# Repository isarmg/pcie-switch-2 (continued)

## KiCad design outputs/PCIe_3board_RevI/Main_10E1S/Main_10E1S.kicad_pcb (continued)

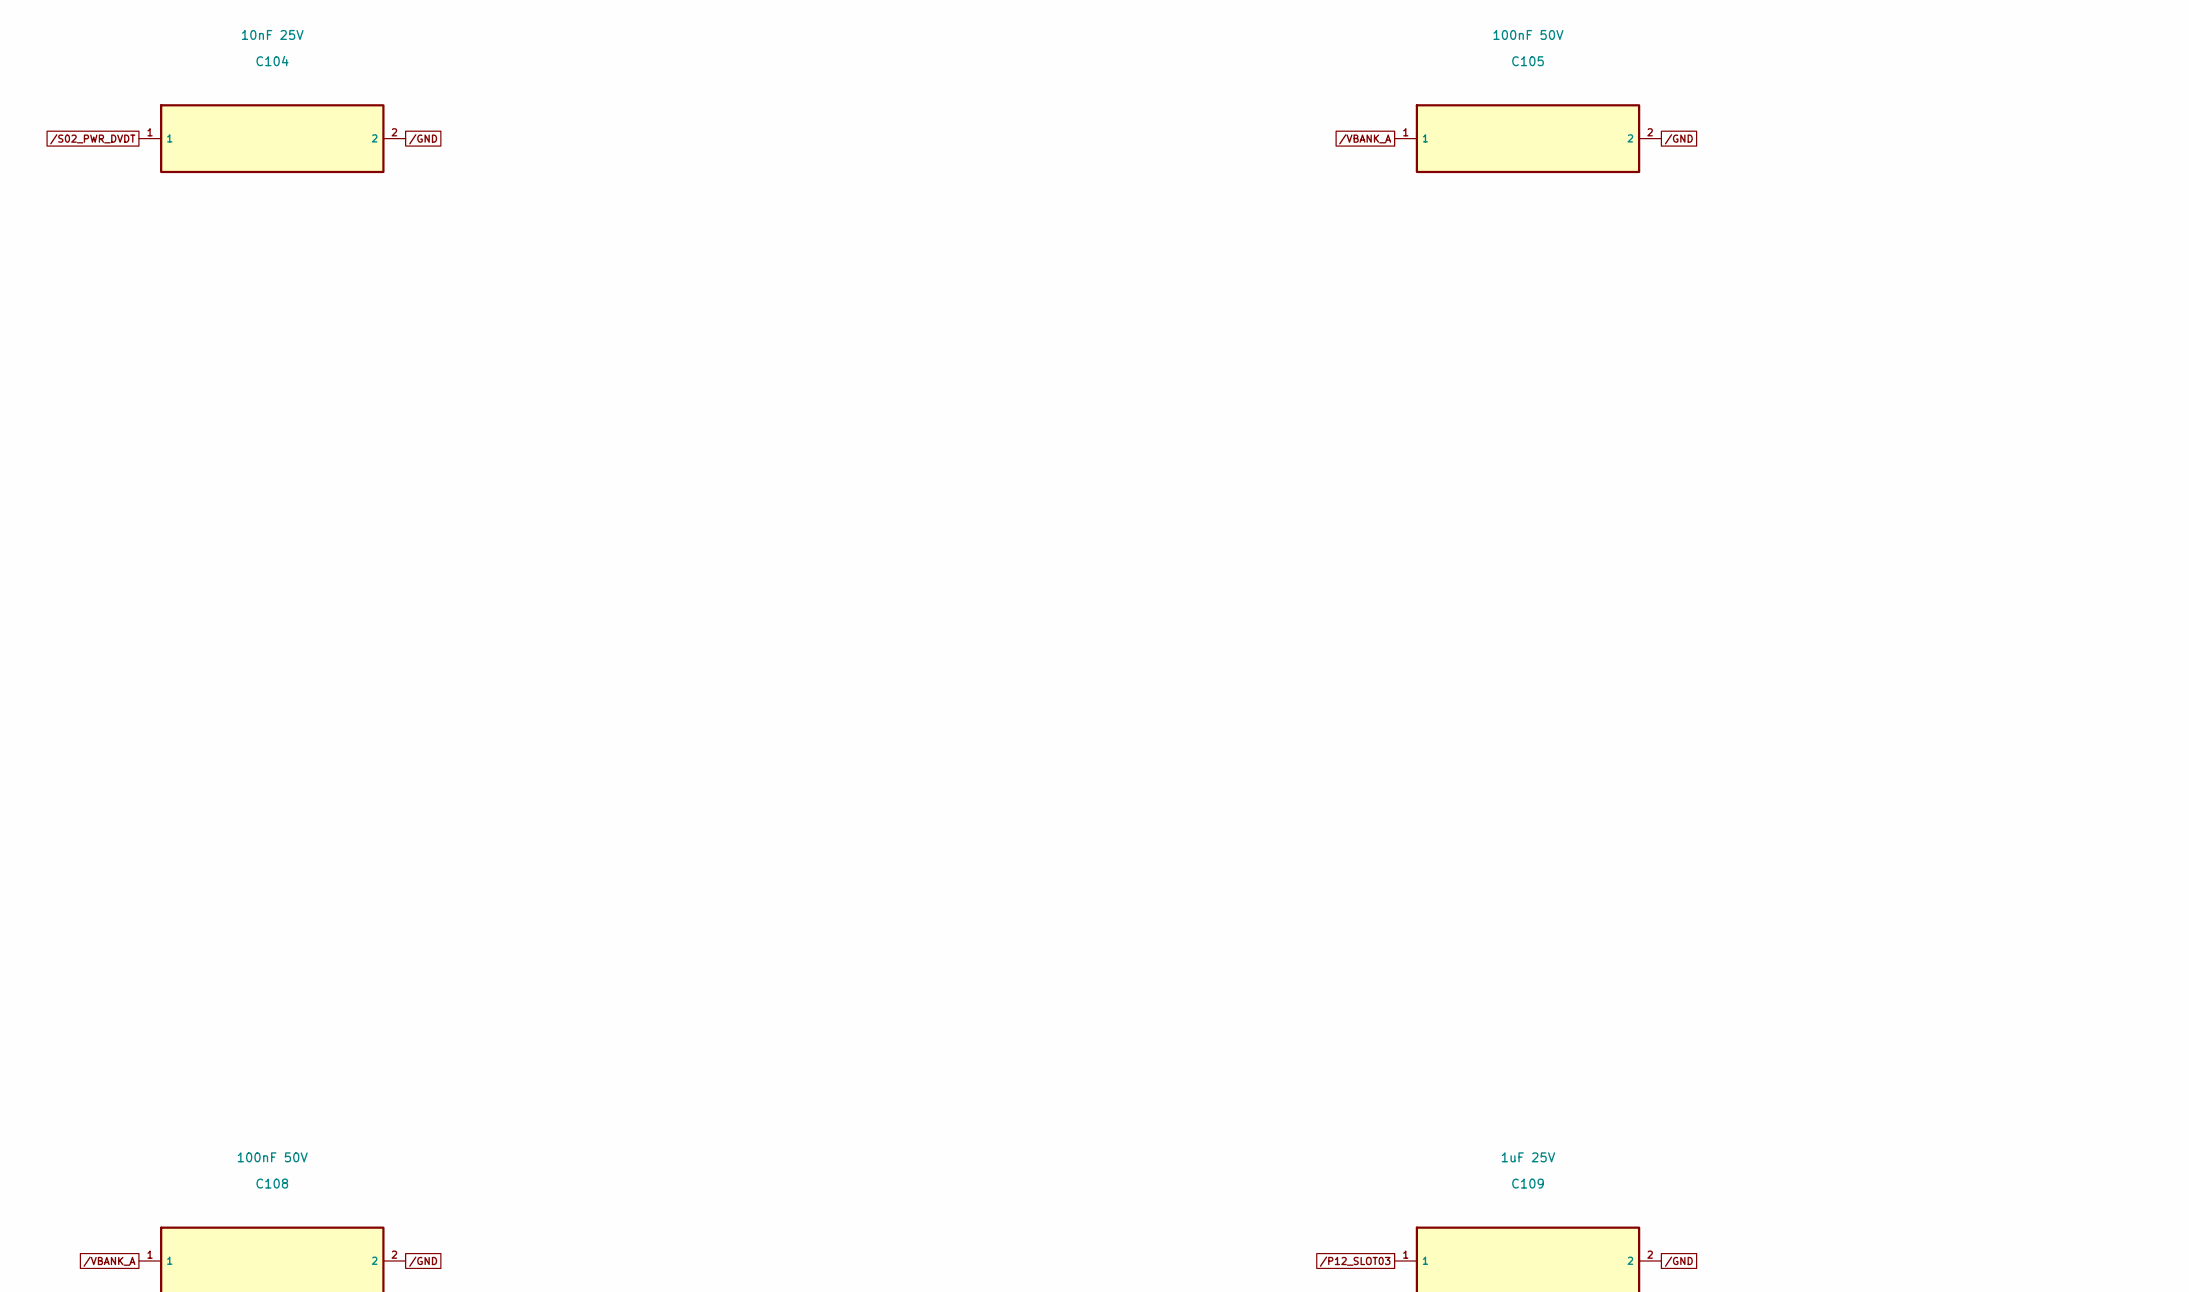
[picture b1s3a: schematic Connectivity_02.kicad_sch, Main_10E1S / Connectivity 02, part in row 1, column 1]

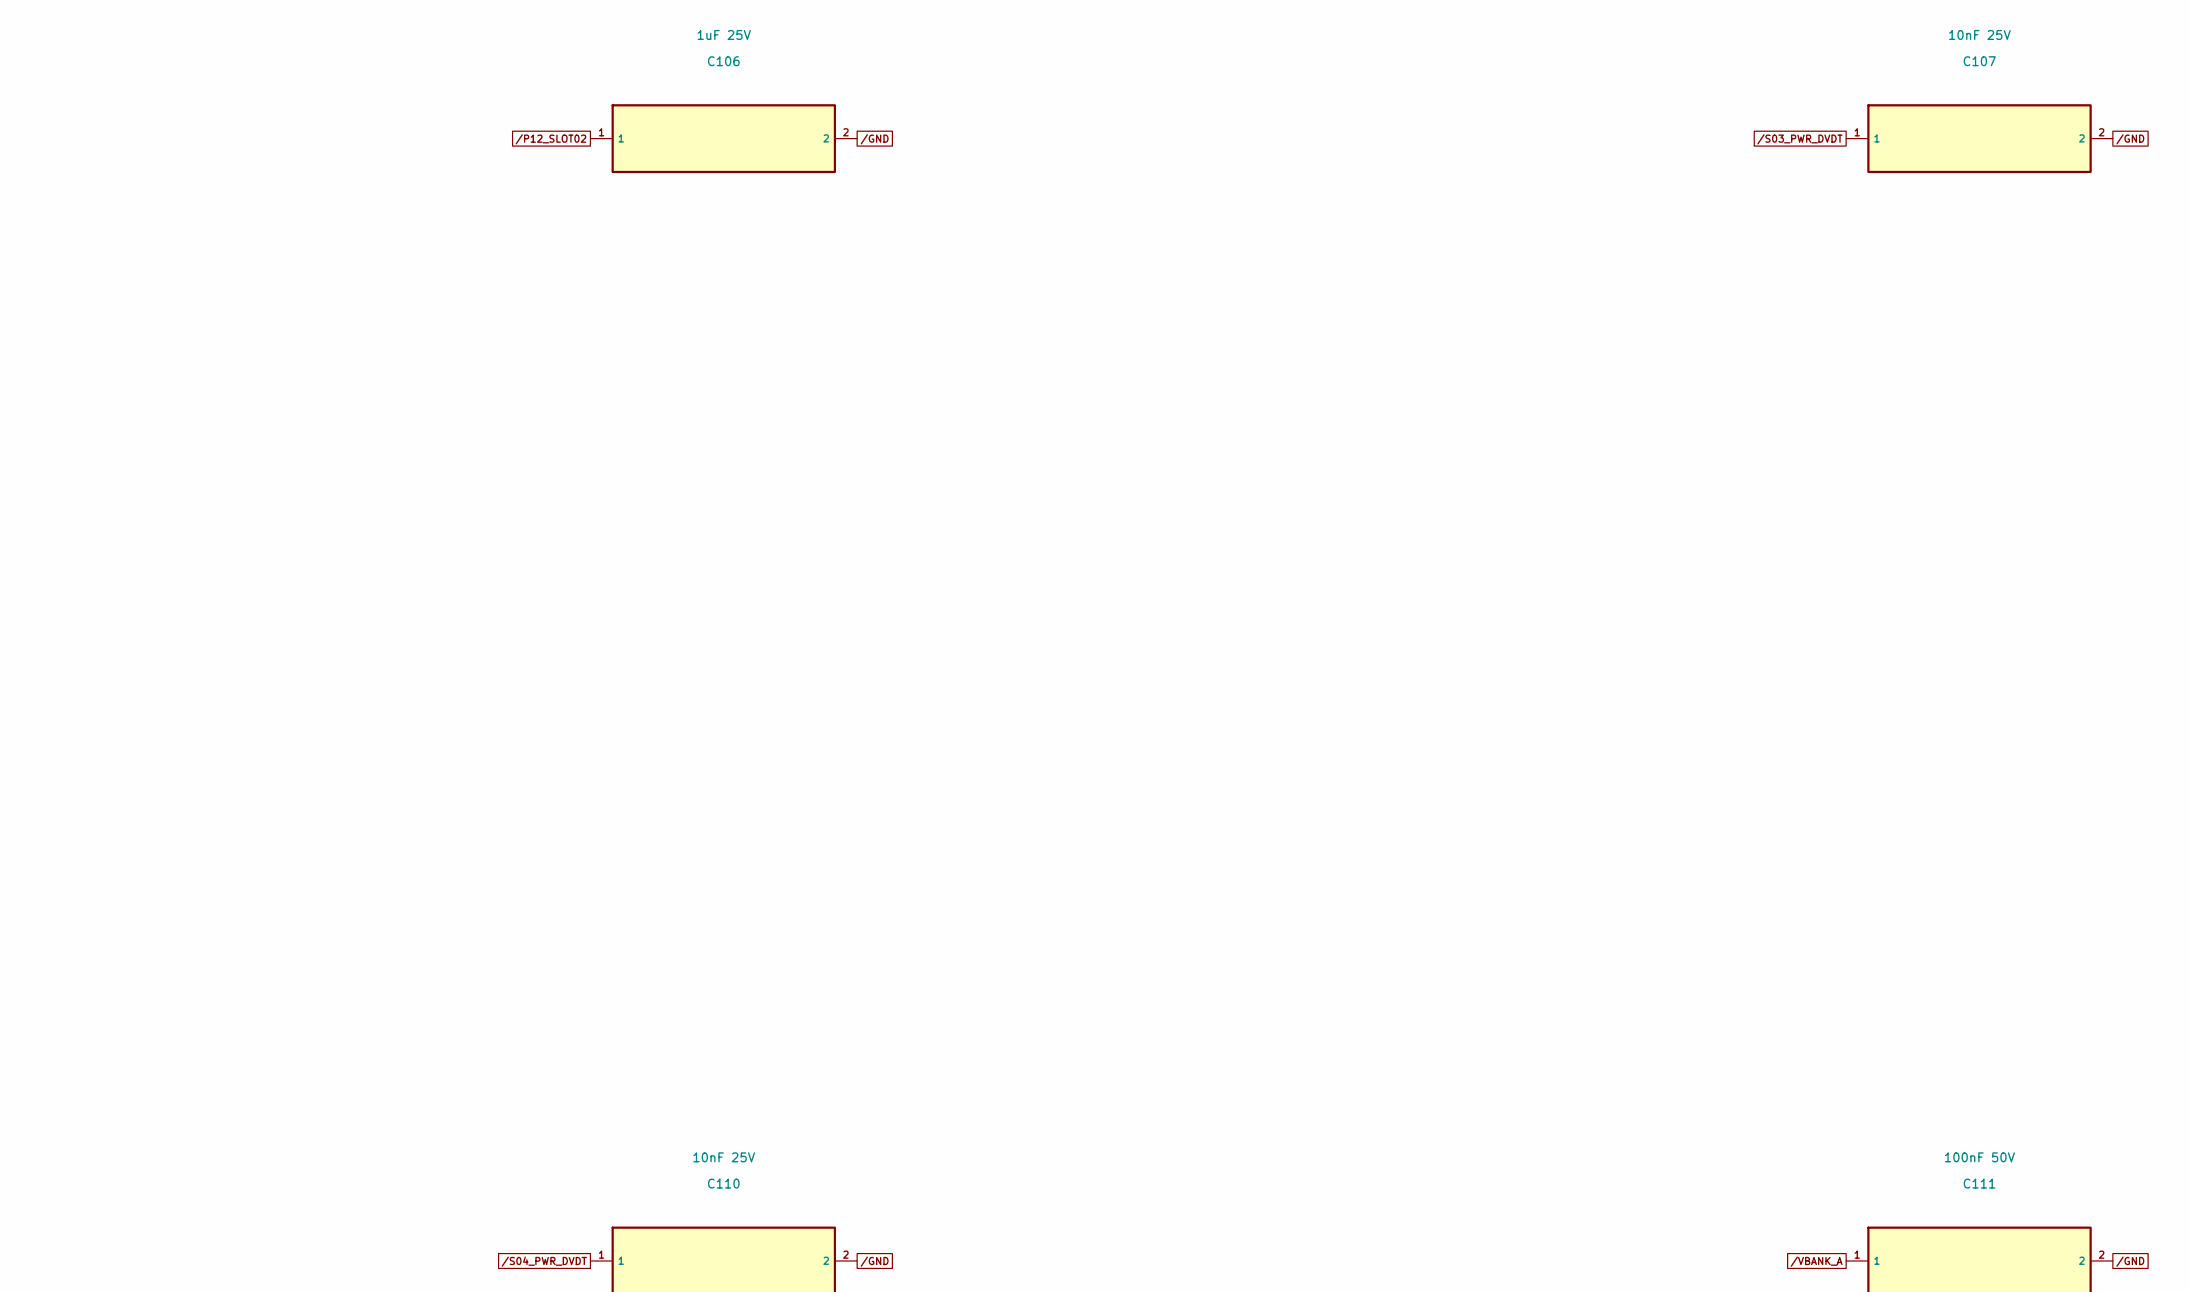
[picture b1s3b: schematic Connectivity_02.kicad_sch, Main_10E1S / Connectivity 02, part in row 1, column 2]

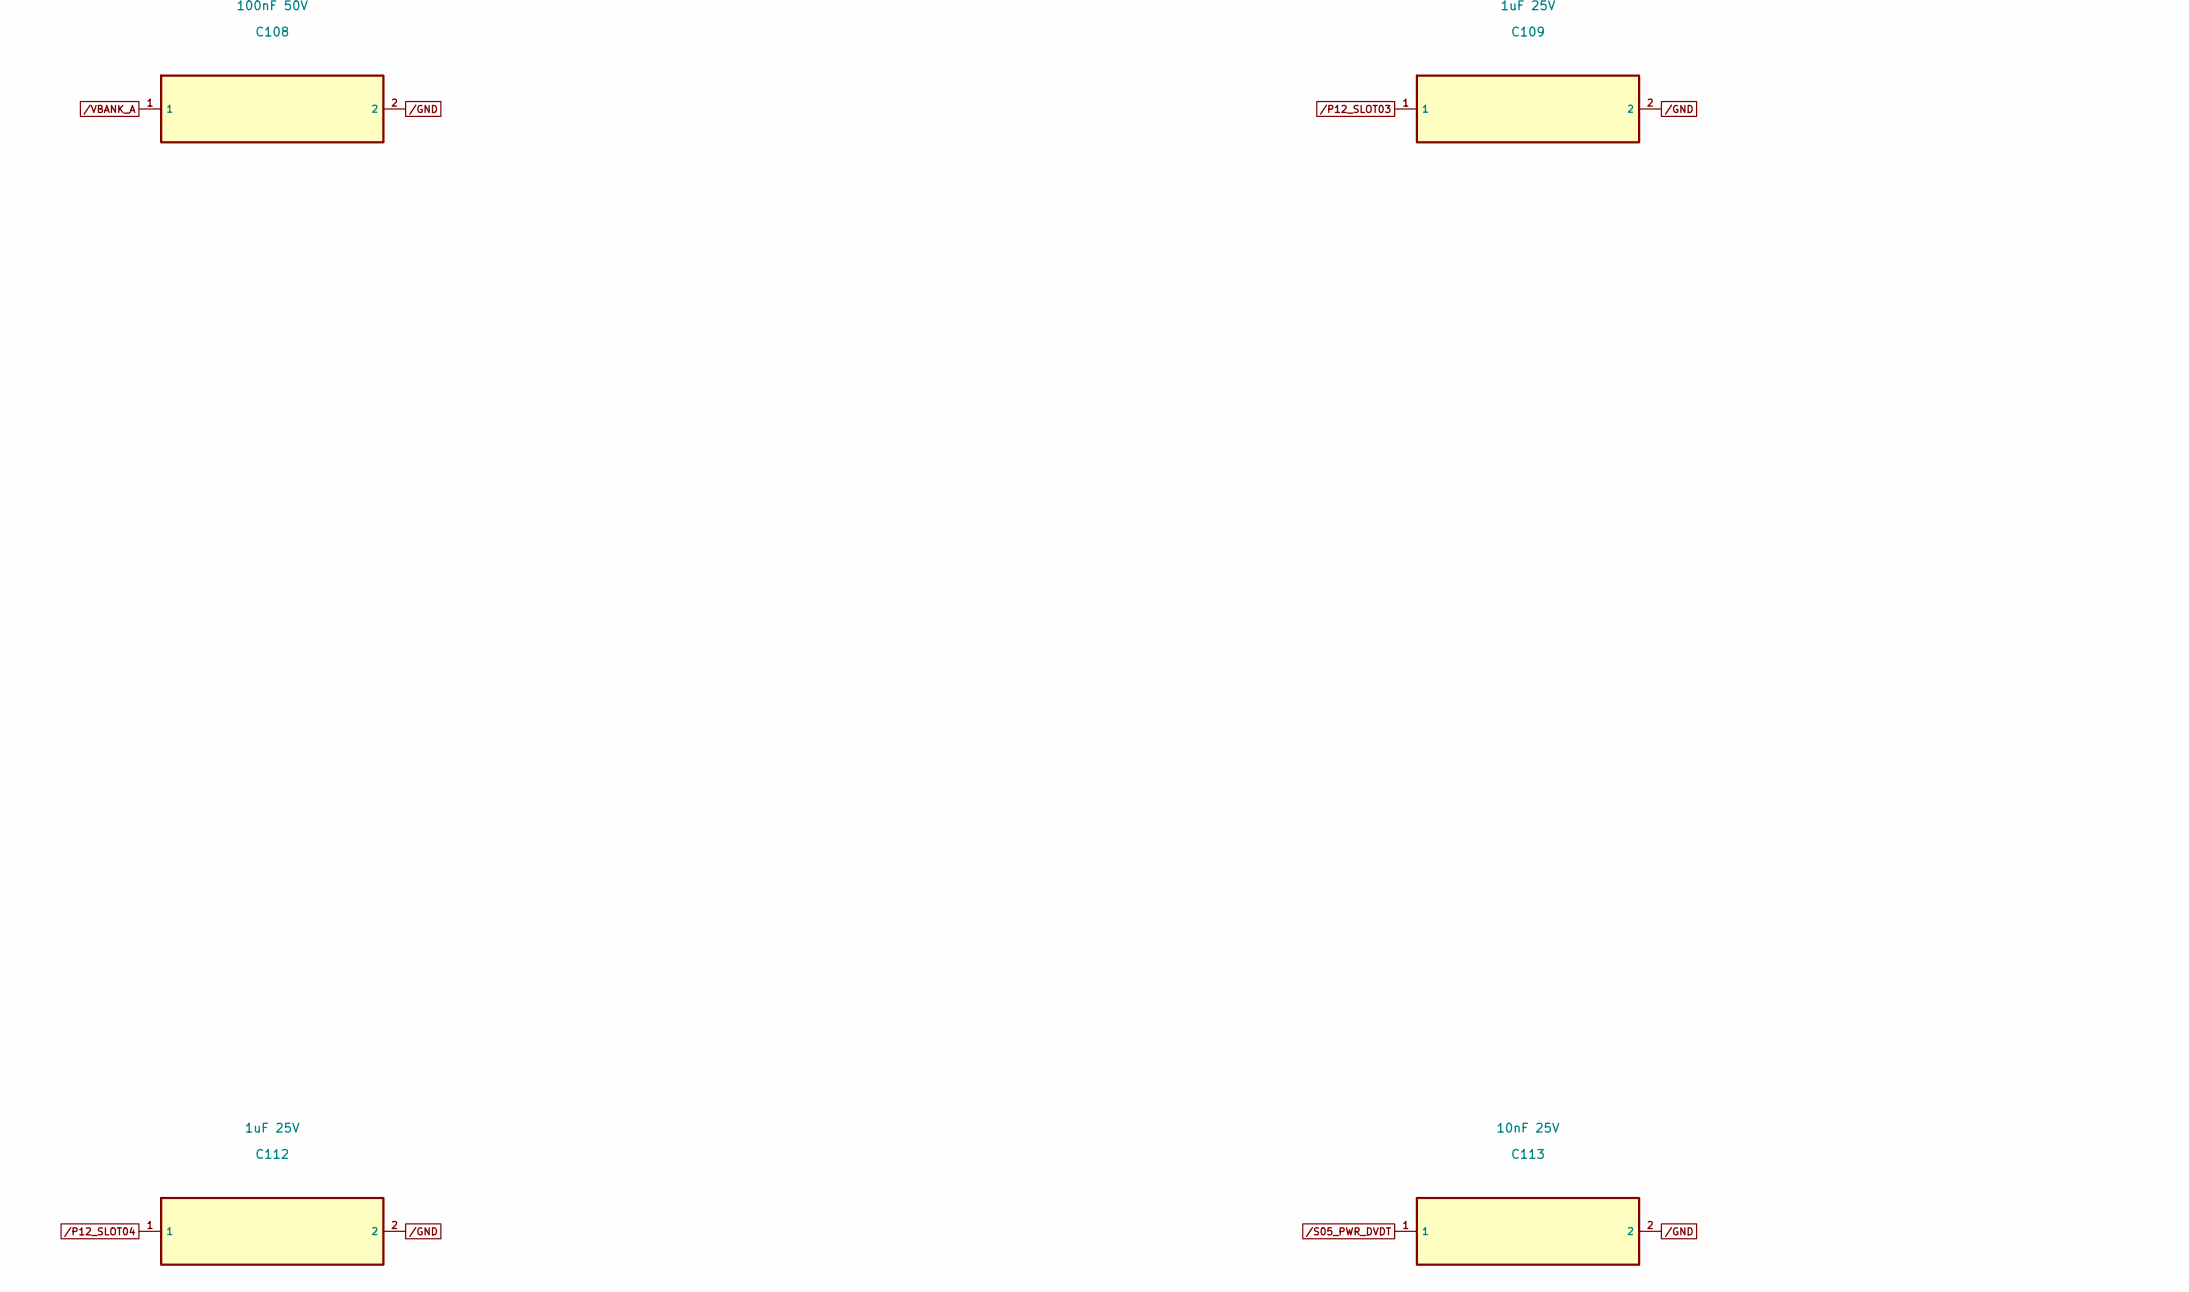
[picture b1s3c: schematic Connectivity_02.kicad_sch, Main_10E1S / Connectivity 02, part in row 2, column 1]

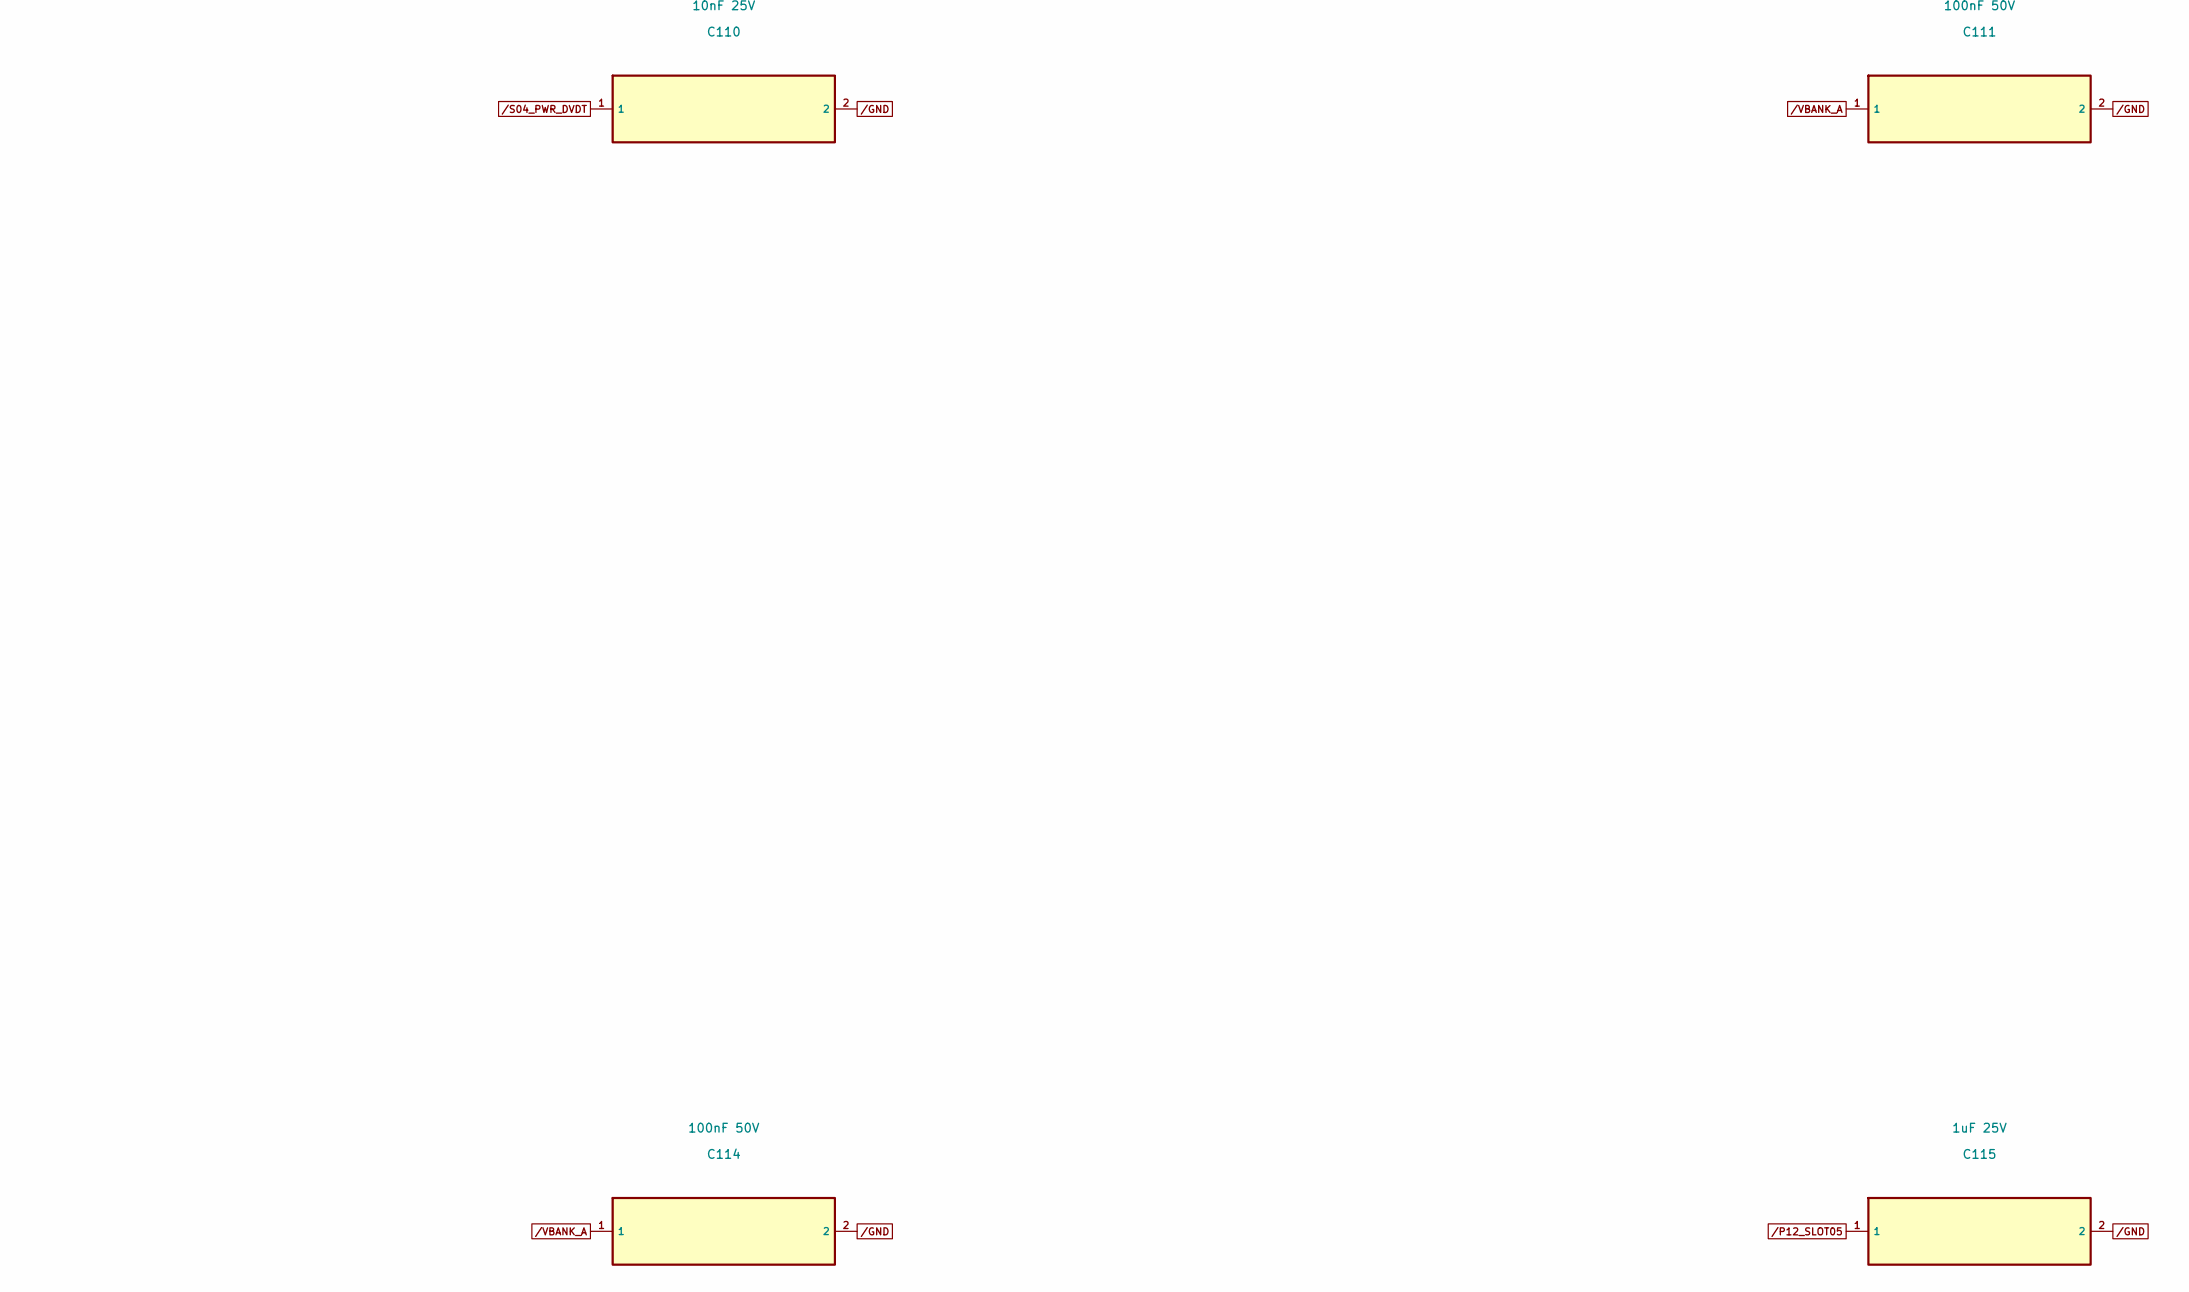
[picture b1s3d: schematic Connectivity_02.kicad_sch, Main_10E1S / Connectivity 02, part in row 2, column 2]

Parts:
C104, C107, C110, C113: 10nF 25V; C_0402_1005Metric
C105, C108, C111, C114: 100nF 50V; C_0603_1608Metric
C106, C109, C112, C115: 1uF 25V; C_0603_1608Metric

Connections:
/GND: C104.2, C105.2, C106.2, C107.2, C108.2, C109.2, C110.2, C111.2, C112.2, C113.2, C114.2, C115.2; also elsewhere on the board
/P12_SLOT02: C106.1; also elsewhere on the board
/P12_SLOT03: C109.1; also elsewhere on the board
/P12_SLOT04: C112.1; also elsewhere on the board
/P12_SLOT05: C115.1; also elsewhere on the board
/S02_PWR_DVDT: C104.1; also elsewhere on the board
/S03_PWR_DVDT: C107.1; also elsewhere on the board
/S04_PWR_DVDT: C110.1; also elsewhere on the board
/S05_PWR_DVDT: C113.1; also elsewhere on the board
/VBANK_A: C105.1, C108.1, C111.1, C114.1; also elsewhere on the board
